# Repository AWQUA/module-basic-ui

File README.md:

# module-basic-ui

### This repo contains the schematic and board layout for a simple, generic user interface consisting of a common 0.96" or 1.3" OLED monitor and three large buttons. Compact, cheap, and breadboard-ready. 

### We bought our buttons from Adafruit (https://www.adafruit.com/product/1010 or https://www.adafruit.com/product/1009) though there are lots of other footprint-compatible options in the Omron B3F button series (see https://octopart.com/search?q=omron%20b3f&start=0). Our OLED monitors currently come from Electrodragon (http://www.electrodragon.com/product/0-96-12864-oled-display-iicspi/), though we'd like to find a monitor of comparable price that is more widely distributed.

### PLEASE NOTE: different versions of the OLED monitors have the GND pin as either the first pin or the second pin. To accommodate, the module includes two footprints for the monitor. Soldering the monitor to the wrong footprint will ensure that the monitor burns out during normal use. Please carefully match your particular monitor to the right footprint -- the ground pins on each footprint are circled.

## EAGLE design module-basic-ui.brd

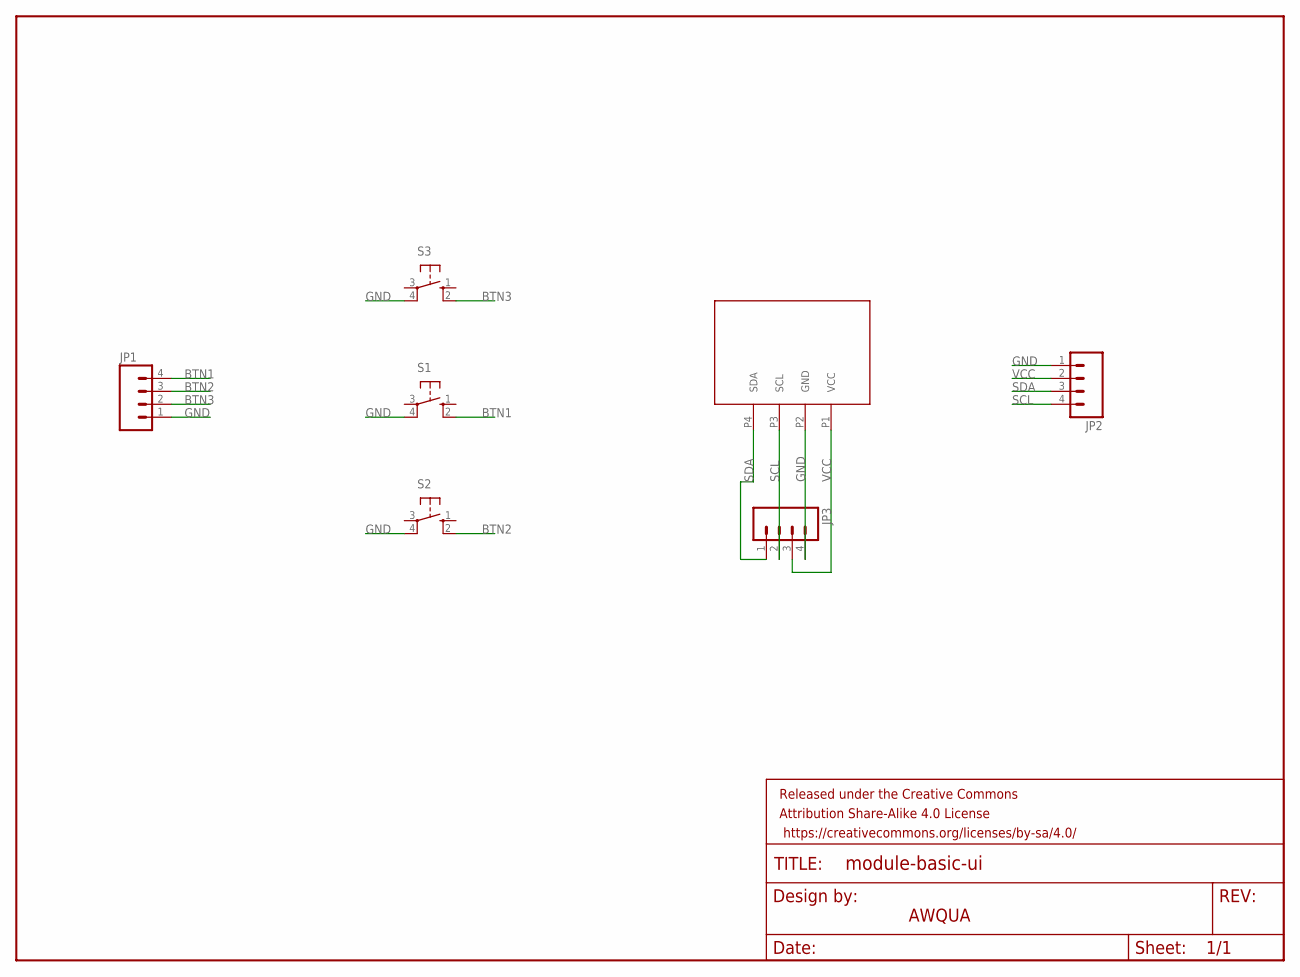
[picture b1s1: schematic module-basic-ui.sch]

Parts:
FRAME1: FRAME-LETTER; CREATIVE_COMMONS
JP1, JP2, JP3: M04PTH; 1X04
S1, S2, S3: 40-XX; B3F-40XX
U$2: I2C-OLED-096

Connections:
BTN1: JP1.4, S1.2 (S1)
BTN2: JP1.3, S2.2 (S1)
BTN3: JP1.2, S3.2 (S1)
GND: JP1.1, JP2.1, JP3.4, S1.4 (P1), S2.4 (P1), S3.4 (P1), U$2.P2 (GND)
SCL: JP2.4, JP3.2, U$2.P3 (SCL)
SDA: JP2.3, JP3.1, U$2.P4 (SDA)
VCC: JP2.2, JP3.3, U$2.P1 (VCC)

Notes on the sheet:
AWQUA

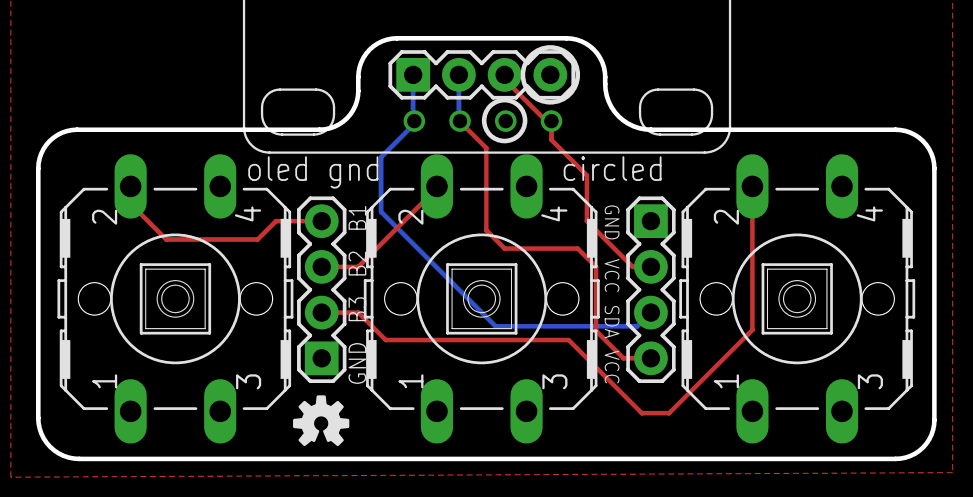
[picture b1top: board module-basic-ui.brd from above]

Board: 2 copper layers, 49.8 x 23.4 mm, 10 parts (1 on the bottom side), 7 nets.

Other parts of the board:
U$1: OSHW-LOGO-S
U$4: OSHW-LOGO-M

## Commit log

2017-09-15 initial push
2017-09-15 board labels tweak

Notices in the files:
parts and their libraries:
SparkFun-Connectors: Licensing: CC v3.0 Share-Alike You are welcome to use this library for commercial purposes.
SparkFun-Aesthetics: Released under the Creative Commons
Attribution Share-Alike 4.0 License
SparkFun-Aesthetics: (https://creativecommons.org/licenses/by-sa/4.0/)
